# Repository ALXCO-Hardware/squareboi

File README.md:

# Squareboi

Squareboi is an open hardware cartridge system for the Game Boy Color, made to be as accessible and DIY-friendly as possible.
Using a handful of off-the-shelf components, it provides the same functionality as an original cartridge, compatible with the majority of programs.
Additionally, an Arduino-based programmer allows for easy transfer of games and save data.

## Features

Up to 4MB ROM/32KB RAM storage space

Stores save data without needing a battery

Made of common, off-the-shelf parts

Fully compatible with MBC1 and MBC5 mappers, partial support for MBC2 and MBC3

Programmer works as a general purpose cartridge reader

Easy to build: A basic version can be made with entirely through-hole components

Powered by a single 5V rail

Compatible with third-party programmers, like the widespread GBxCart RW

## Manual

A thorough explanation of how the system works, and how to assemble it, can be found in the manual file, [HERE.](/Manual.pdf)

## Acknowledgements

Squareboi's existence is only possible due to the continued efforts of multiple individuals dedicated to reverse engineering and documenting the Game Boy hardware.
A full list of those whose work I've built upon can be found within the manual.

Still, I'd like to say it again: Thanks to all of you! I wouldn't have gotten here alone.

## Links

[Official video assembly guide](https://www.youtube.com/playlist?list=PL5rO9JlAGJ3c4BWqF0iWA5yTH4LZhnxgb)

[Squareboi featured on Hackaday](https://hackaday.com/2022/08/16/squareboi-is-the-diy-game-boy-cart-youve-always-wanted/)

## License

Squareboi is the work of a hobbyist – And while significant care was 
taken to make it reliable, I cannot guarantee that it will work in 
your specific use case, or that it will be compatible with your 
hardware.

Squareboi is licensed under the Creative Commons Attribution 4.0 
International License (CC BY 4.0). 
https://creativecommons.org/licenses/by/4.0/#deed-conditions

In essence, if you share or adapt this work, you must credit the 
author (ALXCO), and provide a link to the Squareboi repository, at:
https://github.com/ALXCO-Hardware/squareboi

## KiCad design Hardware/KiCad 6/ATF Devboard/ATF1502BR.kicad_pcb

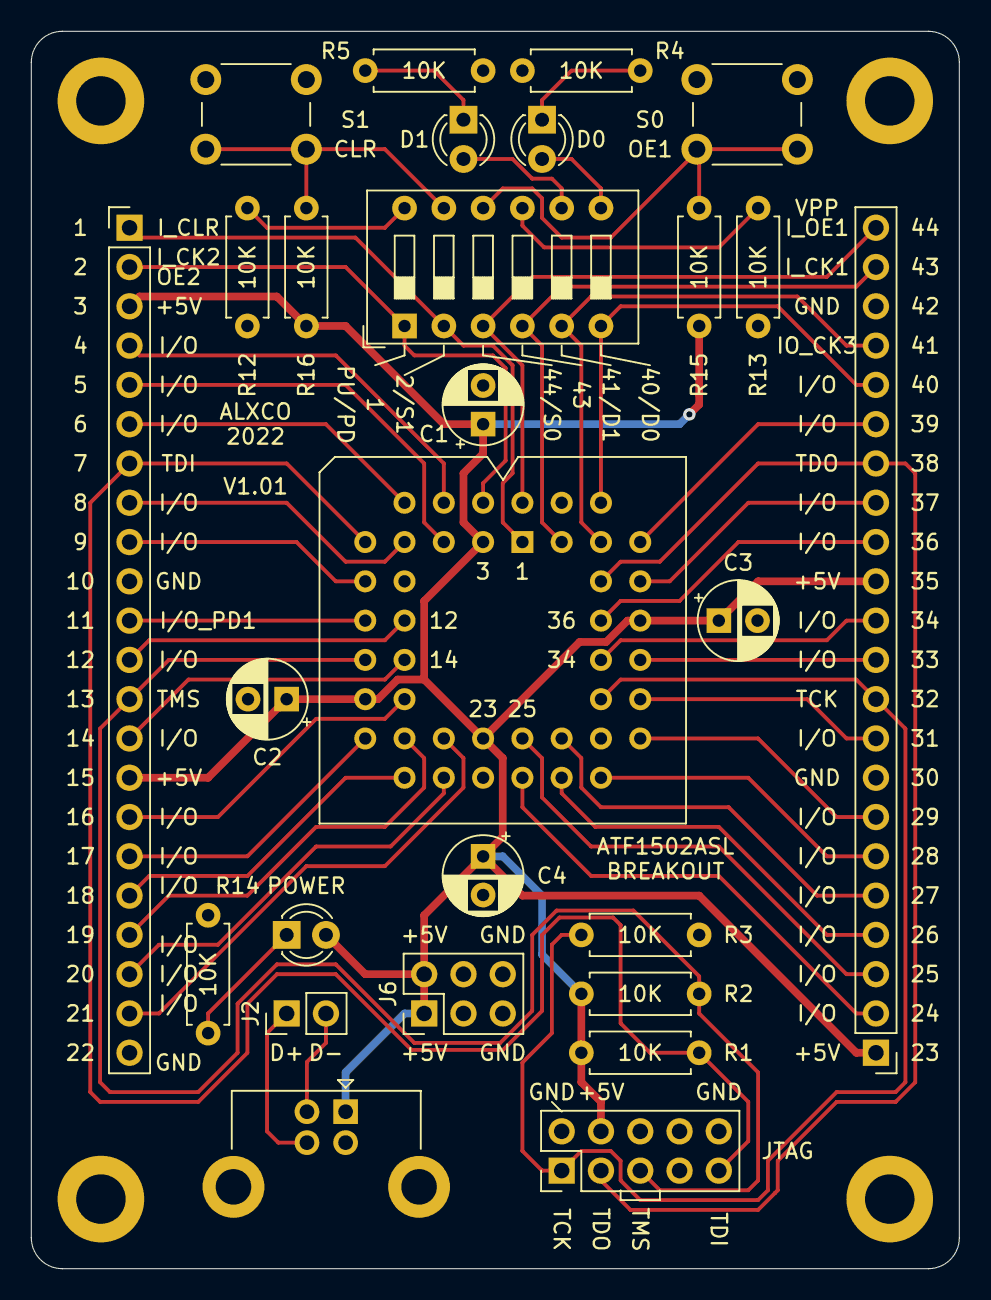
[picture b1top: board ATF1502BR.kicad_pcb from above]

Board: 2 copper layers, 60.0 x 80.0 mm, 27 parts (0 on the bottom side), 49 nets.

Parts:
C1, C2, C3, C4: 220nF; CP_Radial_D5.0mm_P2.50mm
D0, D1, D8: LED; LED_D3.0mm
J1: USB_B; USB_B_Lumberg_2411_02_Horizontal
J2: Conn_01x02; PinHeader_1x02_P2.54mm_Vertical
J3, J5: Conn_01x22; PinHeader_1x22_P2.54mm_Vertical
J4: Conn_02x05_Odd_Even; PinHeader_2x05_P2.54mm_Vertical
J6: Conn_02x05_Odd_Even; PinHeader_2x03_P2.54mm_Vertical
R1, R2, R3, R4, R5, R12, R13, R14, R15, R16: 10K; R_Axial_DIN0207_L6.3mm_D2.5mm_P7.62mm_Horizontal
SW1: SW_DIP_x06; SW_DIP_SPSTx06_Slide_9.78x17.42mm_W7.62mm_P2.54mm
SW4, SW5: SW_Push; SW_PUSH_6mm_H5mm
U1: ATF1502-PLCC; PLCC-44_THT-Socket

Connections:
+5V: C1.1, C2.1, C3.1, C4.1, D8.2, J1.1, J3.3, J3.15, J4.4, J5.1, J5.13, J6.1, J6.2, R1.1, R2.1, R15.1, R16.1, U1.3, U1.15, U1.23, U1.35
/IO_4: J3.4, U1.4
/IO_5: J3.5, U1.5
/IO_6: J3.6, U1.6
/IO_8: J3.8, U1.8
/IO_9: J3.9, U1.9
/IO_12: J3.12, U1.12
/IO_14: J3.14, U1.14
/IO_16: J3.16, U1.16
/IO_17: J3.17, U1.17
/IO_18: J3.18, U1.18
/IO_19: J3.19, U1.19
/IO_20: J3.20, U1.20
/IO_21: J3.21, U1.21
/IO_24: J5.2, U1.24
/IO_26: J5.4, U1.26
/IO_27: J5.5, U1.27
/IO_28: J5.6, U1.28
/IO_29: J5.7, U1.29
/IO_31: J5.9, U1.31
/IO_33: J5.11, U1.33
/IO_34: J5.12, U1.34
/IO_36: J5.14, U1.36
/IO_37: J5.15, U1.37
/IO_39: J5.17, U1.39
/IO_40: J5.18, SW1.6, U1.40
/IO_GCLK3: J5.19, SW1.5, U1.41
/IO_PD1: J3.11, U1.11
/IO_PD2: J5.3, U1.25
/I_GCLK1: J5.21, SW1.4, U1.43
/I_GCLK2_OE2: J3.2, SW1.1, U1.2
/I_GCLR: J3.1, SW1.2, U1.1
/I_OE1: J5.22, SW1.3, U1.44
/LED0: D0.2, SW1.7
/LED1: D1.2, SW1.8
/SW_GCLR: R16.2, SW1.11, SW5.1
/SW_OE1: R15.2, SW1.10, SW4.1
/TCK: J4.1, J5.10, R3.2, U1.32
/TDI: J3.7, J4.9, R1.2, U1.7
/TDO: J4.3, J5.16, U1.38
/TMS: J3.13, J4.5, R2.2, U1.13
/USBN: J1.2, J2.2
/USBP: J1.3, J2.1
GND: C1.2, C2.2, C3.2, C4.2, J1.4, J1.5, J3.10, J3.22, J4.2, J4.10, J5.8, J5.20, J6.5, J6.6, R3.1, R4.2, R5.2, R12.2, R13.2, R14.2, SW4.2, SW5.2, U1.10, U1.22, U1.30, U1.42
unnamed: D0.1, R4.1
unnamed: D1.1, R5.1
unnamed: D8.1, R14.1
unnamed: R12.1, SW1.12
unnamed: R13.1, SW1.9

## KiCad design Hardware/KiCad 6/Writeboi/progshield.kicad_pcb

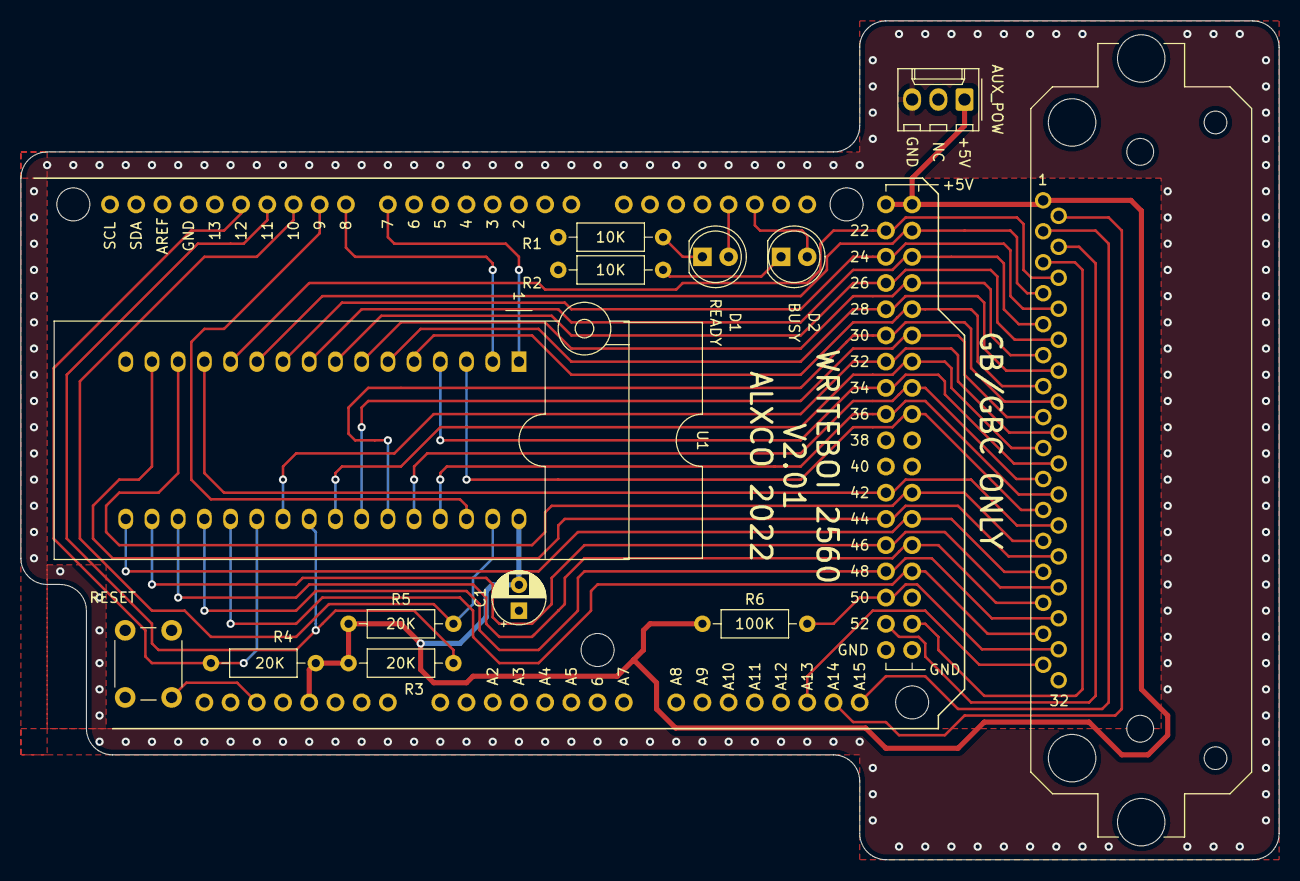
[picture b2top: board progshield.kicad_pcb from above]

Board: 2 copper layers, 121.9 x 81.3 mm, 14 parts (0 on the bottom side), 43 nets.

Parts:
C1: 100n; CP_Radial_D5.0mm_P2.50mm
D1, D2: LED; LED_D5.0mm
J1: GB-CART; GameBoy_Cartridge_DMG_1x32_P1.50mm_Socket_Horizontal
J2: AUX_POW; Molex_KK-254_AE-6410-03A_1x03_P2.54mm_Vertical
R1, R2: 10K; R_Axial_DIN0207_L6.3mm_D2.5mm_P10.16mm_Horizontal
R3, R4, R5: 20K; R_Axial_DIN0207_L6.3mm_D2.5mm_P10.16mm_Horizontal
R6: 100K; R_Axial_DIN0207_L6.3mm_D2.5mm_P10.16mm_Horizontal
SW1: SW_Push; SW_PUSH_6mm_H5mm
U1: SST39SF040; DIP_Socket-32_W11.9_W12.7_W15.24_W17.78_W18.5_3M_232-1285-0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
XA1: Arduino_Mega2560_Shield

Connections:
+5V: C1.2, J1.1, J2.1, R3.1, R4.1, R5.1, R6.1, U1.32, XA1.5V1, XA1.5V3, XA1.5V4
/A0: J1.6, U1.12, XA1.D22
/A1: J1.7, U1.11, XA1.D23
/A2: J1.8, U1.10, XA1.D24
/A3: J1.9, U1.9, XA1.D25
/A4: J1.10, U1.8, XA1.D26
/A5: J1.11, U1.7, XA1.D27
/A6: J1.12, U1.6, XA1.D28
/A7: J1.13, U1.5, XA1.D29
/A8: J1.14, U1.27, XA1.D30
/A9: J1.15, U1.26, XA1.D31
/A10: J1.16, U1.23, XA1.D32
/A11: J1.17, U1.25, XA1.D33
/A12: J1.18, U1.4, XA1.D34
/A13: J1.19, U1.28, XA1.D35
/A14: J1.20, U1.29, XA1.D36
/A15: J1.21, U1.3, XA1.D37
/A16: U1.2, XA1.D8
/A17: U1.30, XA1.D9
/A18: U1.1, XA1.D7
/CLK: J1.2, XA1.A14
/CRT_CS_N: J1.5, XA1.D53
/CRT_PG_N: J1.31, XA1.A13
/CRT_RD_N: J1.4, XA1.D52
/CRT_WR_N: J1.3, XA1.A15
/D0: J1.22, U1.13, XA1.D42
/D1: J1.23, U1.14, XA1.D43
/D2: J1.24, U1.15, XA1.D44
/D3: J1.25, U1.17, XA1.D45
/D4: J1.26, U1.18, XA1.D46
/D5: J1.27, U1.19, XA1.D47
/D6: J1.28, U1.20, XA1.D48
/D7: J1.29, U1.21, XA1.D49
/DIP_CE_N: R4.2, U1.22, XA1.D12
/DIP_OE_N: R3.2, U1.24, XA1.D11
/DIP_WE_N: R5.2, U1.31, XA1.D10
/LED_BY: D2.2, XA1.D19
/LED_RY: D1.2, XA1.D18
/RST_N: J1.30, R6.2, XA1.D50
GND: C1.1, J1.32, J2.3, R1.2, R2.2, SW1.2, U1.16, XA1.GND1, XA1.GND2, XA1.GND3, XA1.GND5, XA1.GND6
unnamed: D1.1, R1.1
unnamed: D2.1, R2.1
unnamed: SW1.1, XA1.RST1

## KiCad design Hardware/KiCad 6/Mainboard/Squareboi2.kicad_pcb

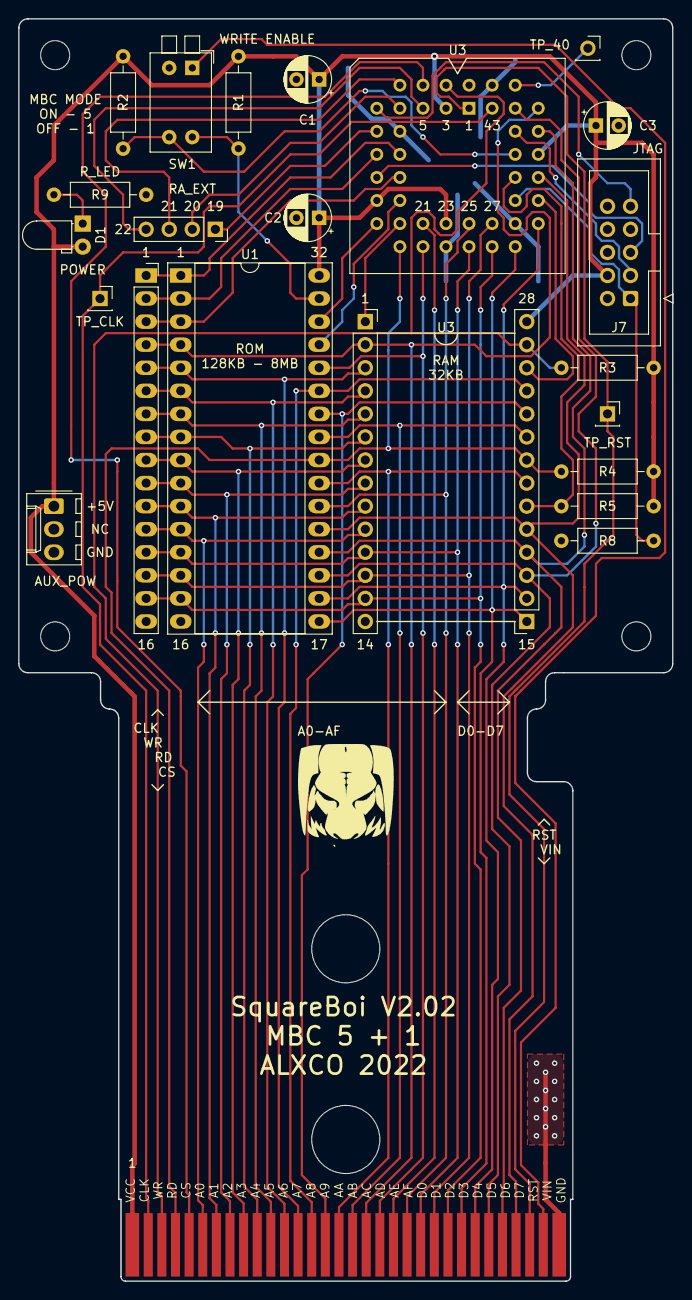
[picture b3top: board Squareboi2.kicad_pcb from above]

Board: 2 copper layers, 72.0 x 139.0 mm, 24 parts (0 on the bottom side), 52 nets.

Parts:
C1, C2, C3: 100n; CP_Radial_D5.0mm_P2.50mm
D1: LED; LED_D3.0mm_Horizontal_O1.27mm_Z2.0mm
J1: GB-CART; GB_CART_FINGERS
J2: ROMC_L; PinSocket_1x16_P2.54mm_Vertical
J4: ROMC_C; PinSocket_1x04_P2.54mm_Vertical
J5: RAMC_L; PinSocket_1x14_P2.54mm_Vertical
J6: RAMC_R; PinSocket_1x14_P2.54mm_Vertical
J7: JTAG; IDC-Header_2x05_P2.54mm_Vertical
J8: AUX_POW; Molex_KK-254_AE-6410-03A_1x03_P2.54mm_Vertical
J10: TP_CLK; PinSocket_1x01_P2.54mm_Vertical
J11: TP_40; PinSocket_1x01_P2.54mm_Vertical
J12: TP_RST; PinSocket_1x01_P2.54mm_Vertical
R1, R2, R3, R4, R5, R8, R9: 20K; R_Axial_DIN0207_L6.3mm_D2.5mm_P10.16mm_Horizontal
SW1: SW_DIP_x02; SW_DIP_SPSTx02_Piano_10.8x6.64mm_W7.62mm_P2.54mm
U1: SST39SF040; DIP-32_W15.24mm_Socket_LongPads
U3: ATF1502AS-PLCC; PLCC-44_THT-Socket

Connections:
+5V: C1.1, C2.1, C3.1, D1.2, J1.1, J6.14, J7.4, J8.1, R1.1, R2.2, R3.1, R4.1, R5.1, U1.32, U3.3, U3.15, U3.23, U3.35
/A0: J1.6, J2.12, J5.10, U1.12
/A1: J1.7, J2.11, J5.9, U1.11
/A2: J1.8, J2.10, J5.8, U1.10
/A3: J1.9, J2.9, J5.7, U1.9
/A4: J1.10, J2.8, J5.6, U1.8
/A5: J1.11, J2.7, J5.5, U1.7
/A6: J1.12, J2.6, J5.4, U1.6
/A7: J1.13, J2.5, J5.3, U1.5
/A8: J1.14, J6.11, U1.27
/A9: J1.15, J6.10, U1.26
/A10: J1.16, J6.7, U1.23
/A11: J1.17, J6.9, U1.25
/A12: J1.18, J2.4, J5.2, U1.4, U3.39
/A13: J1.19, U1.28, U3.20
/A14: J1.20, U3.21
/A15: J1.21, U1.22, U3.25
/AA13: J6.12, U3.31
/AA14: J5.1, U3.19
/CS_N: J1.5, U3.4
/D0: J1.22, J2.13, J5.11, U1.13, U3.24
/D1: J1.23, J2.14, J5.12, U1.14, U3.27
/D2: J1.24, J2.15, J5.13, U1.15, U3.26
/D3: J1.25, J6.1, U1.17, U3.28
/D4: J1.26, J6.2, U1.18, U3.29
/D5: J1.27, J6.3, U1.19, U3.41
/D6: J1.28, J6.4, U1.20, U3.37
/D7: J1.29, J6.5, U1.21, U3.33
/GBCLK: J1.2, J10.1, U3.43
/IO40: J11.1, U3.40
/MODE: R2.1, SW1.3, U3.36
/RA14: U1.29, U3.16
/RA15: J2.3, U1.3, U3.14
/RA16: J2.2, U1.2, U3.11
/RA17: U1.30, U3.17
/RA18: J2.1, U1.1, U3.12
/RA19: J4.1, U3.9
/RA20: J4.2, U3.8
/RA21: J4.3, U3.6
/RA22: J4.4, U3.5
/RAMCS_N: J6.6, R5.2, U3.34
/RD_N: J1.4, J6.8, R4.2, U1.24, U3.18
/ROMWR_N: R1.2, SW1.4, U1.31
/RS_N: J1.30, J12.1, U3.1
/TCK: J7.1, R8.1, U3.32
/TDI: J7.9, U3.7
/TDO: J7.3, U3.38
/TMS: J7.5, U3.13
/VIN: J1.31, SW1.1
/WR_N: J1.3, J6.13, R3.2, U3.2
GND: C1.2, C2.2, C3.2, J1.32, J2.16, J5.14, J7.2, J7.10, J8.3, R8.2, R9.2, SW1.2, U1.16, U3.10, U3.22, U3.30, U3.42, U3.44
unnamed: D1.1, R9.1

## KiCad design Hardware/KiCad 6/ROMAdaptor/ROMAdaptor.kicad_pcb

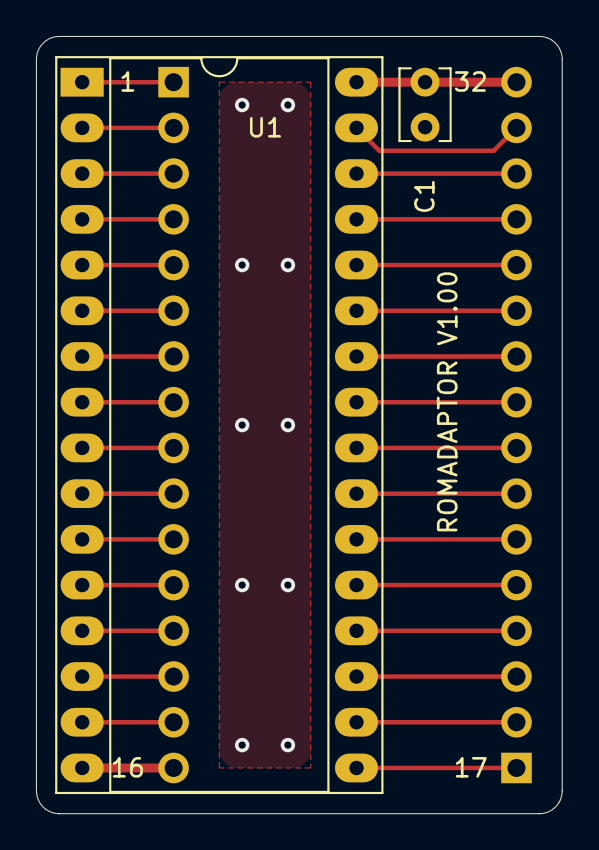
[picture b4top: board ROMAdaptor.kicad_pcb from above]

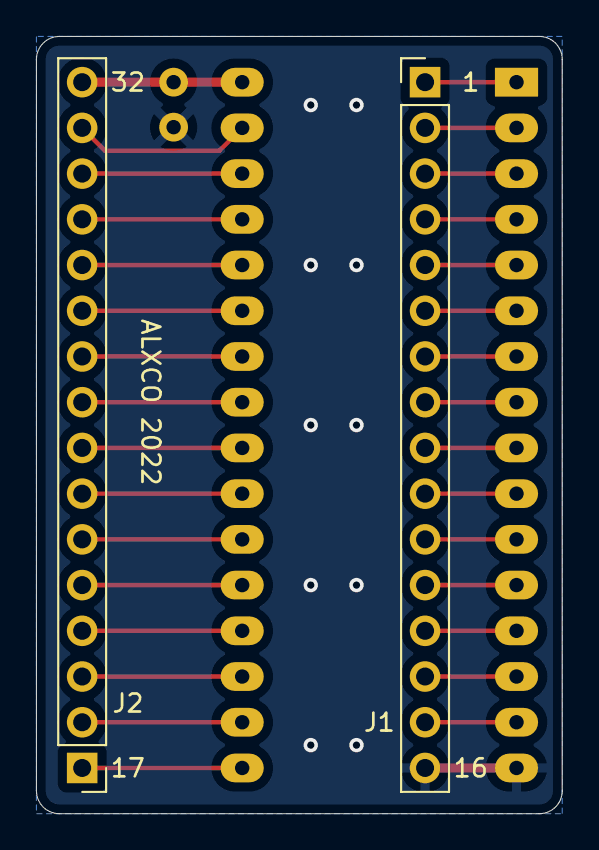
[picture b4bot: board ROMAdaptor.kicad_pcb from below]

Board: 2 copper layers, 29.2 x 43.2 mm, 4 parts (2 on the bottom side), 32 nets.

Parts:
C1: 100n; C_Disc_D3.8mm_W2.6mm_P2.50mm
J1, J2: Conn_01x16; PinHeader_1x16_P2.54mm_Vertical
U1: SST39SF040; DIP-32_W15.24mm_Socket_LongPads

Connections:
+5V: C1.1, J2.16, U1.32
/A0: J1.12, U1.12
/A1: J1.11, U1.11
/A2: J1.10, U1.10
/A3: J1.9, U1.9
/A4: J1.8, U1.8
/A5: J1.7, U1.7
/A6: J1.6, U1.6
/A7: J1.5, U1.5
/A8: J2.11, U1.27
/A9: J2.10, U1.26
/A10: J2.7, U1.23
/A11: J2.9, U1.25
/A12: J1.4, U1.4
/A13: J2.12, U1.28
/A14: J2.13, U1.29
/A15: J1.3, U1.3
/A16: J1.2, U1.2
/A17: J2.14, U1.30
/A18: J1.1, U1.1
/D0: J1.13, U1.13
/D1: J1.14, U1.14
/D2: J1.15, U1.15
/D3: J2.1, U1.17
/D4: J2.2, U1.18
/D5: J2.3, U1.19
/D6: J2.4, U1.20
/D7: J2.5, U1.21
/RD_N: J2.8, U1.24
/ROMCS_N: J2.6, U1.22
/WR_N: J2.15, U1.31
GND: C1.2, J1.16, U1.16

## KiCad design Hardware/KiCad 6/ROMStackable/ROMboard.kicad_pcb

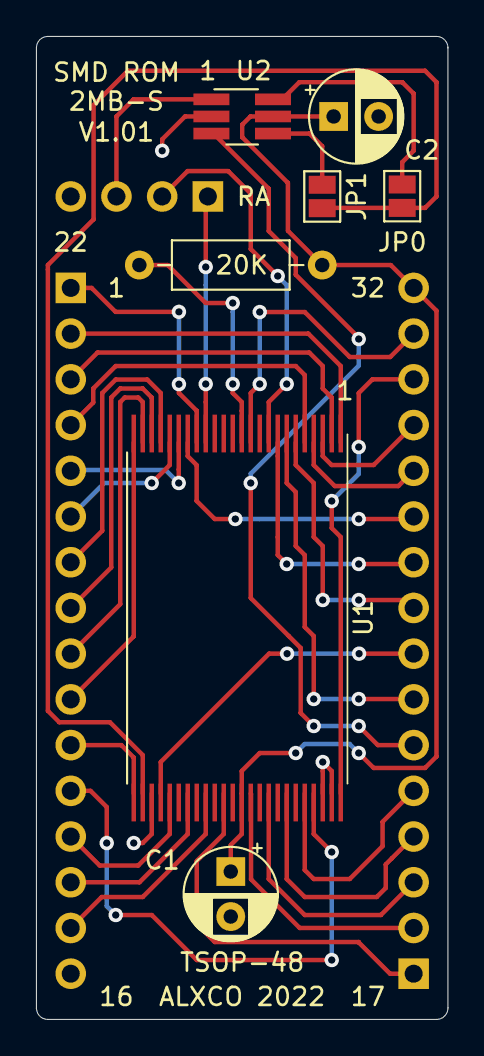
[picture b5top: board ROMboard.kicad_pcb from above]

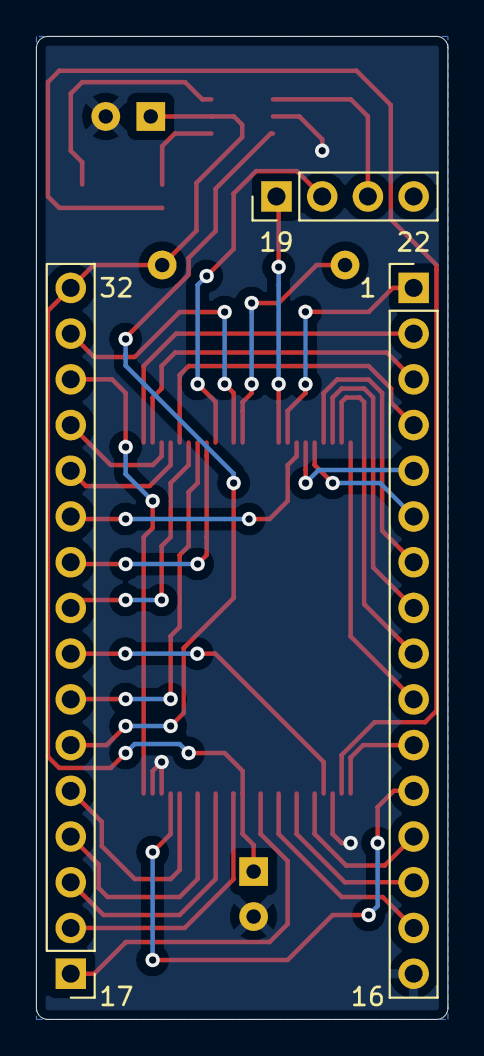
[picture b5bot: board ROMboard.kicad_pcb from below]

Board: 2 copper layers, 22.9 x 54.6 mm, 10 parts (3 on the bottom side), 39 nets.

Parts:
C1, C2: 100n; CP_Radial_D5.0mm_P2.50mm
J0, J1: Conn_01x16; PinHeader_1x16_P2.54mm_Vertical
J2: Conn_01x04; PinHeader_1x04_P2.54mm_Vertical
JP0, JP1: Jumper_2_Open; SolderJumper-2_P1.3mm_Open_Pad1.0x1.5mm
R1: 20K; R_Axial_DIN0207_L6.3mm_D2.5mm_P10.16mm_Horizontal
U1: M29F160; TSOP-I-48_18.4x12mm_P0.5mm
U2: 74LVC1G19; TSOT-23-6_HandSoldering

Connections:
+5V: C1.1, C2.1, J1.16, R1.1, U1.37, U2.5
/A0: J0.12, U1.45
/A1: J0.11, U1.25
/A2: J0.10, U1.24
/A3: J0.9, U1.23
/A4: J0.8, U1.22
/A5: J0.7, U1.21
/A6: J0.6, U1.20
/A7: J0.5, U1.19
/A8: J1.11, U1.18
/A9: J1.10, U1.8
/A10: J1.7, U1.7
/A11: J1.9, U1.6
/A12: J0.4, U1.5
/A13: J1.12, U1.4
/CE_N: J1.6, U2.3
/CE_OUT_N: JP0.2, JP1.2, U1.26
/D0: J0.13, U1.29
/D1: J0.14, U1.31
/D2: J0.15, U1.33
/D3: J1.1, U1.35
/D4: J1.2, U1.38
/D5: J1.3, U1.40
/D6: J1.4, U1.42
/D7: J1.5, U1.44
/RA14: J1.13, U1.3
/RA15: J0.3, U1.2
/RA16: J0.2, U1.1
/RA17: J1.14, U1.48
/RA18: J0.1, U1.17
/RA19: J2.1, U1.16
/RA20: J2.2, U1.9
/RA21: J2.3, U2.1
/RD_N: J1.8, U1.28
/ROMWR_N: J1.15, U1.11
/RST_N: R1.2, U1.12
GND: C1.2, C2.2, J0.16, U1.27, U1.46, U1.47, U2.2
unnamed: JP0.1, U2.6
unnamed: JP1.1, U2.4

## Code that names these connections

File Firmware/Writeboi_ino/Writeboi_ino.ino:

//Writeboi firmware
//V1.00
//For use with Writeboi board V2.01

//ALXCO 2022


//Global build ID:
byte GLB_buildID = 0x01;


//PINOUTS!

#define GB_A0 22
#define GB_A1 23
#define GB_A2 24
#define GB_A3 25
#define GB_A4 26
#define GB_A5 27
#define GB_A6 28
#define GB_A7 29
#define GB_A8 30
#define GB_A9 31
#define GB_A10 32
#define GB_A11 33
#define GB_A12 34
#define GB_A13 35
#define GB_A14 36
#define GB_A15 37

#define DIP_A16 8
#define DIP_A17 9
#define DIP_A18 7

#define GB_D0 42
#define GB_D1 43
#define GB_D2 44
#define GB_D3 45
#define GB_D4 46
#define GB_D5 47
#define GB_D6 48
#define GB_D7 49

#define DIP_CE_N 12
#define DIP_OE_N 11
#define DIP_WE_N 10

#define CRT_CS_N 53
#define CRT_RD_N 52
#define CRT_WR_N A15
#define CRT_PG_N A13
#define CRT_RST_N 50
#define CRT_CLK A14

#define LED_BY 19
#define LED_RY 18

//Compile-time definitions!

#define ARRSIZE 1024

//Globals!
unsigned long GLB_MBCROMBank = 0;
bool GLB_MBCROMBankValid = false;
unsigned long GLB_MBCRAMBank = 0;
bool GLB_MBCRAMBankValid = false;



byte GLB_bytearray[ARRSIZE] = {};

//Lookup table for inverting a byte
//Use with the following code to reverse a variable X:
//X = (GLB_reverselookup[ X & 0b1111] << 4) | GLB_reverselookup[X>>4];
byte GLB_reverselookup[16] = {
0x0, 0x8, 0x4, 0xc, 0x2, 0xa, 0x6, 0xe,
0x1, 0x9, 0x5, 0xd, 0x3, 0xb, 0x7, 0xf, };


//Port manip pin-setting macros!


//CRT_CS_N:PIN53:PB0
#define PM_CRT_CS_N_HIGH() PORTB=PORTB|0b00000001
#define PM_CRT_CS_N_LOW()  PORTB=PORTB&0b11111110

//CRT_RD_N:PIN52:PB1

#define PM_CRT_RD_N_HIGH() PORTB=PORTB|0b00000010
#define PM_CRT_RD_N_LOW()  PORTB=PORTB&0b11111101

//CRT_WR_N:PINA15:PK7
#define PM_CRT_WR_N_HIGH() PORTK=PORTK|0b10000000
#define PM_CRT_WR_N_LOW()  PORTK=PORTK&0b01111111


//CRT_PG_N:PINA13:PK5
#define PM_CRT_PG_N_HIGH() PORTK=PORTK|0b00100000
#define PM_CRT_PG_N_LOW()  PORTK=PORTK&0b11011111



//DIP_CE_N:PIN12:PB6
#define PM_DIP_CE_N_HIGH() PORTB=PORTB|0b01000000
#define PM_DIP_CE_N_LOW()  PORTB=PORTB&0b10111111

//DIP_OE_N:PIN11:PB5
#define PM_DIP_OE_N_HIGH() PORTB=PORTB|0b00100000
#define PM_DIP_OE_N_LOW()  PORTB=PORTB&0b11011111

//DIP_WE_N:PIN10:PB4
#define PM_DIP_WE_N_HIGH() PORTB=PORTB|0b00010000
#define PM_DIP_WE_N_LOW()  PORTB=PORTB&0b11101111





void setup() {
  // Set all control lines to an inactive state
  digitalWrite(DIP_CE_N, HIGH);
  digitalWrite(DIP_OE_N, HIGH);
  digitalWrite(DIP_WE_N, HIGH);
  pinMode(DIP_CE_N, OUTPUT);
  pinMode(DIP_OE_N, OUTPUT);
  pinMode(DIP_WE_N, OUTPUT);

  digitalWrite(CRT_CS_N, HIGH);
  digitalWrite(CRT_RD_N, HIGH);
  digitalWrite(CRT_WR_N, HIGH);
  digitalWrite(CRT_PG_N, HIGH);
  digitalWrite(CRT_CLK, LOW);

  pinMode(CRT_CS_N, OUTPUT);
  pinMode(CRT_RD_N, OUTPUT);
  pinMode(CRT_WR_N, OUTPUT);
  pinMode(CRT_PG_N, OUTPUT);
  pinMode(CRT_CLK, OUTPUT);

  setDataPinMode(INPUT);


  pinMode(GB_A0, OUTPUT);
  pinMode(GB_A1, OUTPUT);
  pinMode(GB_A2, OUTPUT);
  pinMode(GB_A3, OUTPUT);
  pinMode(GB_A4, OUTPUT);
  pinMode(GB_A5, OUTPUT);
  pinMode(GB_A6, OUTPUT);
  pinMode(GB_A7, OUTPUT);
  pinMode(GB_A8, OUTPUT);
  pinMode(GB_A9, OUTPUT);
  pinMode(GB_A10, OUTPUT);
  pinMode(GB_A11, OUTPUT);
  pinMode(GB_A12, OUTPUT);
  pinMode(GB_A13, OUTPUT);
  pinMode(GB_A14, OUTPUT);
  pinMode(GB_A15, OUTPUT);
  
  pinMode(DIP_A16, OUTPUT);
  pinMode(DIP_A17, OUTPUT);
  pinMode(DIP_A18, OUTPUT);

  //LED test, reset cartridge
  digitalWrite(LED_RY, HIGH);
  digitalWrite(LED_BY, HIGH);
  pinMode(LED_BY, OUTPUT);
  pinMode(LED_RY, OUTPUT);
  digitalWrite(CRT_RST_N, LOW);
  pinMode(CRT_RST_N, OUTPUT);


  delay(1500);

  digitalWrite(LED_RY, LOW);
  digitalWrite(LED_BY, LOW);
  pinMode(CRT_RST_N, INPUT);

  initializeByteArray();
  
  delay(50);

  GLB_MBCROMBank = 0;
  GLB_MBCRAMBank = 0;
  GLB_MBCROMBankValid = false;
  GLB_MBCRAMBankValid = false;  

  delay(500);


  
  Serial.begin(115200);
  setBusy(false);





}

void loop() {
  // put your main code here, to run repeatedly:
  serialManager();
}

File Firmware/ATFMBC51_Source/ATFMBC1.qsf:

# -------------------------------------------------------------------------- #
#
# Copyright (C) 1991-2013 Altera Corporation
# Your use of Altera Corporation's design tools, logic functions 
# and other software and tools, and its AMPP partner logic 
# functions, and any output files from any of the foregoing 
# (including device programming or simulation files), and any 
# associated documentation or information are expressly subject 
# to the terms and conditions of the Altera Program License 
# Subscription Agreement, Altera MegaCore Function License 
# Agreement, or other applicable license agreement, including, 
# without limitation, that your use is for the sole purpose of 
# programming logic devices manufactured by Altera and sold by 
# Altera or its authorized distributors.  Please refer to the 
# applicable agreement for further details.
#
# -------------------------------------------------------------------------- #
#
# Quartus II 64-Bit
# Version 13.0.1 Build 232 06/12/2013 Service Pack 1 SJ Web Edition
# Date created = 21:20:45  December 04, 2021
#
# -------------------------------------------------------------------------- #
#
# Notes:
#
# 1) The default values for assignments are stored in the file:
#		ATFMBC1_assignment_defaults.qdf
#    If this file doesn't exist, see file:
#		assignment_defaults.qdf
#
# 2) Altera recommends that you do not modify this file. This
#    file is updated automatically by the Quartus II software
#    and any changes you make may be lost or overwritten.
#
# -------------------------------------------------------------------------- #


set_global_assignment -name FAMILY MAX7000S
set_global_assignment -name DEVICE "EPM7032SLC44-10"
set_global_assignment -name TOP_LEVEL_ENTITY ATFMBC1
set_global_assignment -name ORIGINAL_QUARTUS_VERSION "13.0 SP1"
set_global_assignment -name PROJECT_CREATION_TIME_DATE "21:20:45  DECEMBER 04, 2021"
set_global_assignment -name LAST_QUARTUS_VERSION "13.0 SP1"
set_global_assignment -name PROJECT_OUTPUT_DIRECTORY output_files
set_global_assignment -name ERROR_CHECK_FREQUENCY_DIVISOR "-1"
set_global_assignment -name MIN_CORE_JUNCTION_TEMP 0
set_global_assignment -name MAX_CORE_JUNCTION_TEMP 85
set_global_assignment -name VHDL_FILE ATFMBC1.vhd
set_global_assignment -name MAX7000_DEVICE_IO_STANDARD TTL
set_global_assignment -name USE_CONFIGURATION_DEVICE ON
set_location_assignment PIN_2 -to WR_N
set_location_assignment PIN_43 -to GBCLK
set_global_assignment -name SDC_FILE SDC1.sdc
set_location_assignment PIN_1 -to RESET_N
set_location_assignment PIN_20 -to A[13]
set_location_assignment PIN_21 -to A[14]
set_location_assignment PIN_25 -to A[15]
set_location_assignment PIN_19 -to AA[14]
set_location_assignment PIN_31 -to AA[13]
set_location_assignment PIN_4 -to CS_N
set_location_assignment PIN_29 -to D[4]
set_location_assignment PIN_28 -to D[3]
set_location_assignment PIN_26 -to D[2]
set_location_assignment PIN_27 -to D[1]
set_location_assignment PIN_24 -to D[0]
set_location_assignment PIN_12 -to RA[18]
set_location_assignment PIN_17 -to RA[17]
set_location_assignment PIN_11 -to RA[16]
set_location_assignment PIN_14 -to RA[15]
set_location_assignment PIN_16 -to RA[14]
set_location_assignment PIN_34 -to RAM_CS_N
set_location_assignment PIN_18 -to RD_N
set_location_assignment PIN_33 -to D[7]
set_location_assignment PIN_37 -to D[6]
set_location_assignment PIN_41 -to D[5]
set_location_assignment PIN_36 -to MBCMODE
set_location_assignment PIN_5 -to RA[22]
set_location_assignment PIN_6 -to RA[21]
set_location_assignment PIN_8 -to RA[20]
set_location_assignment PIN_9 -to RA[19]
set_location_assignment PIN_32 -to TCK
set_location_assignment PIN_7 -to TDI
set_location_assignment PIN_38 -to TDO
set_location_assignment PIN_13 -to TMS
set_location_assignment PIN_40 -to TP40
set_location_assignment PIN_44 -to TP44
set_location_assignment PIN_39 -to A[12]

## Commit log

2022-07-29 Initial upload
2022-07-29 Create LICENSE
2022-07-29 Update Manual.pdf
    Added 4MB compatibility details to Programmer section
2022-08-01 Fixed missing symbols in mainboard schematic
2022-08-01 Update Manual.pdf
    Added extra information regarding RAM chip selection and final assembly.
2022-08-04 SquareboiGUI updated
    Fixed Force Stop button not working. Re-compiled binaries.
2022-08-07 Update README.md
    Clarified MBC compatibility
2022-08-21 Increase backplate clearance
    Increase backplate and stacking backplate clearance from 4 to 6mm, to better fit SOIC-28 RAM.
2022-08-22 Refactor pullup resistors
    Add pullup to reset line for DMG compatibility, remove TDI and TMS pullups. Update mainboard to V2.02.
2022-08-22 Update Manual.pdf
    Change resistor BOM, add new TDI/TMS pullup compile options for POF2JED.
2022-08-22 Update Manual.pdf
    Update current firmware version number to 2.02
2022-08-22 Update mainboard firmware
    Change JED file to include TDI and TMS pullups, update precompiled version to V2.02.
2022-08-23 Update CPLD firmware to V203
    Recompiled to remove pin keeper option for DMG compatibility.
2022-08-23 Remove reset pullup from Mainboard
    Remove the RS_N pullup resistor after fixing pin keeper issue in software. Repackage corresponding gerbers.
2022-08-23 Update Manual.pdf
    Update manual to reflect V203 firmware, new compile options for POF2JED, removal of RS_N pullup resistor.
2022-09-14 Update README.md
    Add Links section with Hackaday article
2022-09-15 Update README.md
    Add link to video assembly guide
2022-09-15 Update schematic capacitors
    Move capacitor symbols to be closer to devices they're decoupling, fix value typo (10nf to 100nf)
2022-09-15 Reorganize schematic
    Divide schematic into functional blocks, clean up comments
2022-09-15 Update capacitor value
    Specify 100n as the decoupling capacitor value
2022-09-15 Update capacitor value
    Set decoupling capacitor value to 100n
2022-09-15 Update capacitor values
    Set decoupling capacitor values to 100n
2022-09-16 Rework schematic
    Clean up and reorganize schematic into functional blocks
2022-10-09 Create Kicad 5 subfolder
    Move contents of hardware folder into a subfolder, to prepare for eventual update into Kicad 6
2022-10-09 Convert mainboard to Kicad 6 format
2022-10-09 Create Conversion Guidelines.txt
    To be used when converting subprojects from KiCad 5 to 6
2022-10-09 Convert RAMBoard to KiCad 6 format
2022-10-09 Convert ROMBoard to KiCad 6 format
2022-10-09 Convert ROMStackable to KiCad 6
2022-10-09 Convert Writeboi to KiCad 6
2022-10-09 Clean up leftover files
    Remove .lib, .sch-bak files left over from previous conversions.
2022-10-09 Convert ROMAdaptor to KiCad 6
2022-10-09 Convert ATF Devboard to KiCad 6
2022-10-09 Change KiCad 5 folder to legacy
2022-10-09 Update Manual.pdf
    Update paths to gerber files, change recommended KiCad version to 6.
2022-10-12 Adjust orientation of RAMboard headers
    Flip the pin headers to the bottom of the board, to better reflect their actual position when assembled.
2022-10-12 Adjust orientation of ROMboard headers
    Flip the pin headers to the bottom of the board, to better reflect their actual position when assembled. General cleanup of disconnected traces.
2022-10-12 Adjust Orientation of ROMStackable headers
    Flip the pin headers to the bottom of the board, to better reflect their actual position when assembled. General cleanup of disconnected traces.
2022-10-12 Adjust orientation of ROMAdaptor headers
    Flip the pin headers to the bottom of the board, to better reflect their actual position when assembled. General cleanup of disconnected traces.
2022-10-12 Clean up Mainboard traces
    Clean up disconnected traces
2022-10-12 Clean up Writeboi traces
    Clean up disconnected traces
2022-10-12 Clean up ATF Devboard traces
    Clean up disconnected traces
2022-12-03 Set up .gitignore
    Set repository to ignore all the backup folders on KICad 6 projects.
2022-12-04 Add firmware version checking to serial connection
    Make it so pressing the connect button automatically requests the writeboi's build ID, and displays a warning if it's older than the GUI's. Also update logprint function to accept text_color argument.
2022-12-04 Update error log colors
    Update various error log messages to use the new color options on progmanager.logprint()
2022-12-04 Correct build ID typo
2022-12-04 Remove precompiled GUI
    Remove all files related to the compiled GUI. Moving forwards, they will be available using the Release functionality.
2022-12-04 Update Manual.pdf
    Change Flashcart Usage section to reflect the new location of the precompiled WriteboiGUI file.
2023-02-27 Update Manual.pdf
    Add third party programmers section, update acknowledgements
2023-02-27 Update README.md
    Add section about third-party programmers

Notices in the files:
Hardware/KiCad 6/Mainboard/Squareboi2.kicad_pcb:
© Kyra 'nonchip' Zimmer / me@nonchip.de
